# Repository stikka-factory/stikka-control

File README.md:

# Stikka-Controller

A small (42 × 23 mm, 2-layer) carrier board for an **ESP32-S3-WROOM-1** module
that turns a label printer into a network printer for the Stikka sticker
factory. The board runs the [stikka-esp32](https://github.com/stikka-factory/stikka-esp32)
firmware, which receives print jobs over MQTT from the
[stikka-mqtt](https://github.com/stikka-factory/stikka-mqtt) web app and
forwards them to the printer, normally over the printer's own USB port with
the ESP32-S3 acting as a USB host.

```
Browser (stikka-mqtt)  ──MQTT──▶  broker  ──MQTT──▶  Stikka-Controller  ──USB──▶  printer
render label, publish                                 (stikka-esp32 fw)    J7
to /<printer>/command/                                status on /<printer>/status/
```

## Repository contents

| Path | What it is |
|---|---|
| `Stikka-Controller.kicad_pro` / `.kicad_sch` / `.kicad_pcb` | KiCad project, schematic and layout |
| `bom/ibom.html` | Interactive BOM (open in a browser for assembly) |
| `production/Stikka-Controller.zip` | Gerbers + drill files for fabrication |
| `production/netlist.ipc` | IPC-D-356 netlist for fab electrical test |

## Main parts

| Ref | Part | Function |
|---|---|---|
| U1 | ESP32-S3-WROOM-1 | MCU, Wi-Fi. Use the **N16R8** variant (16 MB flash, 8 MB octal PSRAM): the firmware is built for it and needs the PSRAM. |
| U5 | RECOM R-78E5.0-1.0 footprint (schematic value says RBT10W24S05) | Switching regulator, VIN → +5 V. Feeds the printer's USB VBUS, the status LED and the LDO. |
| U2 | AP2127N-3.3 (SOT-23) | LDO, +5 V → +3.3 V for the ESP32. |
| Q1, Q2 + R1, R2 (10k) | SS8050 (SOT-23) | Classic DTR/RTS auto-program circuit, so a USB-UART adapter can reset the ESP32 and put it in download mode. |
| R3 (10k) + C1 (1µ) | | EN pull-up and power-on reset delay. |
| C11–C16 | 1µ / 4µ7 / 10µ, 0603 | Rail decoupling. |
| J7 | Grove-style 4-pin, 2.0 mm, SMD right angle | USB host port to the printer. |
| J4 | 1×5 pin header, 2.54 mm | Programming / debug UART. |
| J6 | 1×3, 2.0 mm (Samtec UMPT footprint) | External WS2812 / NeoPixel status LED. |
| J1, J2, J3 | 2-pad SMD (uses the `L_APV_ANR252010` footprint) | Reset pads, boot pads, power input. |

## Connectors and pinout

### J3: power input

| Pin | Net |
|---|---|
| 1 | VIN |
| 2 | GND |

VIN goes straight into U5. The usable input range depends on the regulator
actually fitted: an R-78E5.0-1.0 takes 7–28 V and gives up to 1 A at 5 V.
That 1 A is shared between the ESP32 and the printer's VBUS. There is no
reverse-polarity protection.

### J7: USB host to the printer

| Pin | Net | ESP32-S3 |
|---|---|---|
| 1 | GND | |
| 2 | +5V (VBUS) | |
| 3 | USB_D- | GPIO19 |
| 4 | USB_D+ | GPIO20 |
| SS1, SS2 | GND (mounting tabs) | |

This is a USB 1.1 full-speed host port on the ESP32-S3's native USB-OTG pins.
It uses a Grove housing, but it is **not I²C**, so don't plug Grove modules
into it. Wire it to a USB-A socket or straight to a USB-B plug for the
printer: GND → pin 4 (black), VBUS → pin 1 (red), D- → pin 2 (white),
D+ → pin 3 (green).

### J4: programming / debug UART

| Pin | Net | ESP32-S3 |
|---|---|---|
| 1 | TXD | GPIO43 (U0TXD), output from the board |
| 2 | RXD | GPIO44 (U0RXD), input to the board |
| 3 | DTR | Q2 emitter, Q1 base via R1 |
| 4 | RTS | Q1 emitter, Q2 base via R2 |
| 5 | GND | |

Connect a 3.3 V USB-UART adapter that exposes DTR and RTS (CP2102, CH340 and
similar): adapter RX → J4 TXD, adapter TX → J4 RXD. With DTR/RTS connected,
esptool, PlatformIO and the web flasher in stikka-mqtt reset the board into
download mode on their own. J4 has no power pin, so power the board through
J3 while flashing.

The same port carries the firmware's debug log at 115200 baud (`pio device
monitor`).

### J6: status LED

| Pin | Net | ESP32-S3 |
|---|---|---|
| 1 | +5V | |
| 2 | LED (data) | GPIO48 |
| 3 | GND | |

For a single WS2812 / NeoPixel (GRB). The LED runs from 5 V while the data
line is 3.3 V, which most WS2812Bs accept but which is below spec
(V<sub>IH</sub> = 0.7 × VDD ≈ 3.5 V). If an LED misbehaves, use a WS2812
variant that is happy with 3.3 V logic, or a level shifter.

### J1, J2: reset and boot pads

| Ref | Pin 1 | Pin 2 | Use |
|---|---|---|---|
| J1 | RST (EN) | GND | Short to reset the ESP32 |
| J2 | BOOT (GPIO0) | GND | Hold shorted while resetting to enter the ROM bootloader |

You only need these if your USB-UART adapter has no DTR/RTS.

### ESP32-S3 GPIO use

| GPIO | Net | Used for |
|---|---|---|
| EN | RST | Reset (R3/C1, Q1, J1) |
| 0 | BOOT | Strapping / download mode (Q2, J2) |
| 19 | USB_D- | USB host to printer (J7) |
| 20 | USB_D+ | USB host to printer (J7) |
| 43 | TXD | UART0 TX (J4) |
| 44 | RXD | UART0 RX (J4) |
| 48 | LED | NeoPixel data (J6) |

All other GPIOs are unconnected and not broken out.

## Firmware: stikka-esp32

Use the single `esp32-s3-devkitc-1` env from stikka-esp32's `platformio.ini`.
It targets the same N16R8 module (`qio_opi` memory type, `BOARD_HAS_PSRAM`,
16 MB partitions), so it runs on this board as is. You can flash it in
either of two ways:

- `pio run -e esp32-s3-devkitc-1 -t upload` from a stikka-esp32 checkout,
  with the USB-UART adapter on J4.
- The in-browser ESP32 flasher in the stikka-mqtt web app, over the same
  adapter.

On first boot the firmware opens a setup Wi-Fi AP, and its web wizard asks
for the printer protocol and connection method. On this board, choose:

| Method | Works on this board? | Notes |
|---|---|---|
| `usb_host` | **Yes**, the intended use | J7. The board supplies VBUS from its own 5 V rail. Covers ZPL, Brother QL and Seiko printers on USB. |
| `network` | Yes | No board hardware involved; the ESP32 talks to a ZPL printer over TCP. |
| `serial` | **No** | No UART for the printer is broken out (see below). |

### Firmware/board pin check

Checked against stikka-esp32 `3e263b6`:

| Function | Firmware | Board | Status |
|---|---|---|---|
| Status LED | NeoPixel on GPIO48, GRB (`DEFAULT_LED_*` in `platformio.ini`) | J6 pin 2 = GPIO48 | ✅ matches |
| Debug log | `Serial` = UART0, 115200 (`ARDUINO_USB_CDC_ON_BOOT=0`, `logging.cpp`) | J4 TXD/RXD = GPIO43/44 | ✅ matches |
| USB host | Native USB-OTG (`usb_host_target.cpp`) | J7 D-/D+ = GPIO19/20, VBUS = +5V | ✅ matches |
| Serial printer | UART2 on `printerUartTxPin=32` / `printerUartRxPin=33` (`config.h`) | Not broken out | ⚠️ GPIO32/33 aren't pins on the WROOM-1 module. On the N16R8 they're used internally by the flash and octal PSRAM, so this default doesn't work on this board, or on any WROOM-1 board. |

## Using it with stikka-mqtt

Once the board is on Wi-Fi and connected to the same MQTT broker as the
stikka-mqtt web app, it publishes a retained status snapshot on
`/<printerName>/status/`. The web app picks that up on its `/+/status/#`
subscription and lists the printer. Print jobs come in on
`/<printerName>/command/`, and the board's status LED shows the connection
state:

| Colour | Meaning |
|---|---|
| Green | Wi-Fi and MQTT connected |
| Yellow | Wi-Fi only |
| Red | No Wi-Fi (setup AP mode) |
| Purple / cyan flash | MQTT message received / sent |

stikka-mqtt's README documents the message format.

## Known issues / open points

- **U5 value vs footprint:** the schematic value is `RBT10W24S05`, but the
  symbol and footprint are RECOM R-78E5.0-1.0. Check which part is actually
  fitted before choosing a supply voltage.
- **J1–J3 footprint:** these use an inductor footprint (`L_APV_ANR252010`) as
  plain 2-pad SMD pads. That's fine electrically, but it's easy to miss in
  the BOM.
- **5 V budget:** with a 1 A regulator, the printer's USB port only gets what
  the ESP32 leaves over (~0.5–0.7 A while Wi-Fi is transmitting). That's
  enough for printers powered from their own supply, but not for
  bus-powered ones.
- **No serial-printer header:** if `serial` support is wanted on this board,
  a later revision would need to break out a free GPIO pair (e.g. GPIO17/18,
  the U1TXD/U1RXD defaults), and the firmware defaults would need to change
  to match.

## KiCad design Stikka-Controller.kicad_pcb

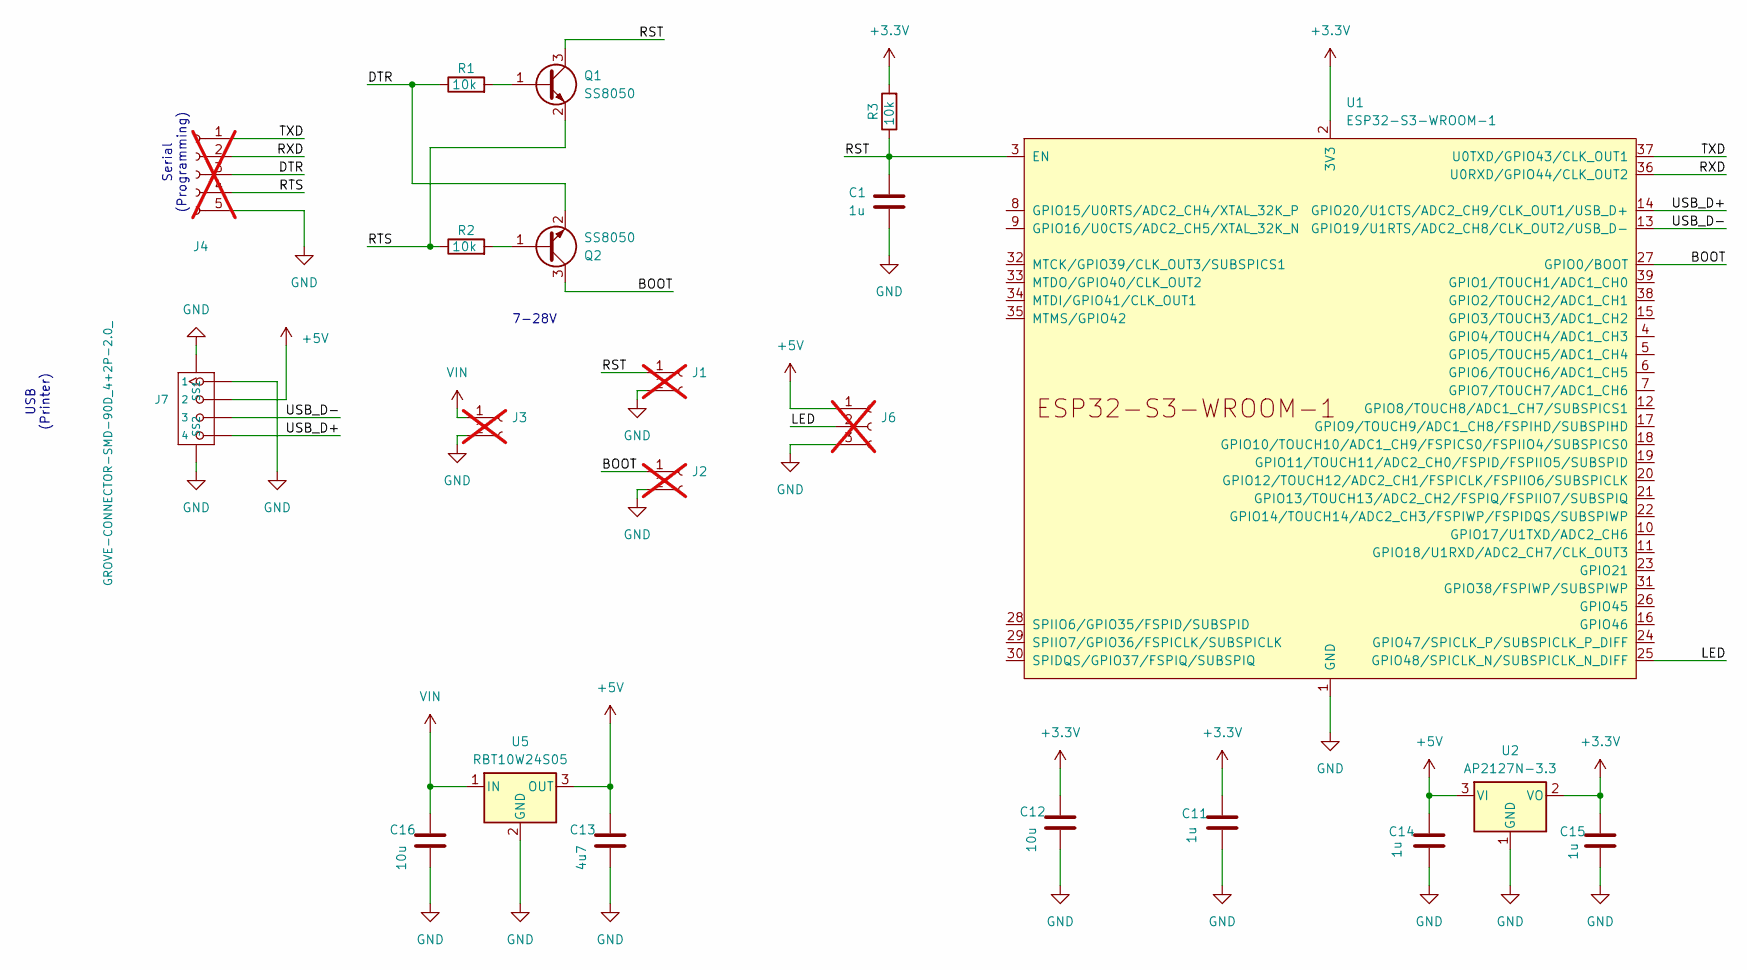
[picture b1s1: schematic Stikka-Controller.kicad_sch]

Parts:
C1, C11, C14, C15: 1u; C_0603_1608Metric_Pad1.08x0.95mm_HandSolder
C12, C16: 10u; C_0603_1608Metric_Pad1.08x0.95mm_HandSolder
C13: 4u7; C_0603_1608Metric_Pad1.08x0.95mm_HandSolder
J1, J2, J3: Conn_01x02_Socket; L_APV_ANR252010; not fitted
J4: Conn_01x05_Socket; PinHeader_1x05_P2.54mm_Vertical; not fitted
J6: Conn_01x03_Socket; Samtec_UMPT-03-XX.X-X-V-S_1x03_P2.0mm_Terminal; not fitted
J7: GROVE-CONNECTOR-SMD-90D_4+2P-2.0_; GROVE-HW4-SMD-2.0-90D
Q1, Q2: SS8050; SOT-23
R1, R2, R3: 10k; R_0603_1608Metric_Pad0.98x0.95mm_HandSolder
U1: ESP32-S3-WROOM-1
U2: AP2127N-3.3; SOT-23
U5: RBT10W24S05; Converter_DCDC_RECOM_R-78E-0.5_THT

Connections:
+3.3V: C11.1, C12.1, C15.1, R3.2, U1.2 (3V3), U2.2 (VO)
+5V: C13.1, C14.1, J6.1, J7.2, U2.3 (VI), U5.3 (OUT)
/BOOT: J2.1, Q2.3 (C), U1.27 (GPIO0/BOOT)
/DTR: J4.3, Q2.2 (E), R1.1
/LED: J6.2, U1.25 (GPIO48/SPICLK_N/SUBSPICLK_N_DIFF)
/RST: C1.1, J1.1, Q1.3 (C), R3.1, U1.3 (EN)
/RTS: J4.4, Q1.2 (E), R2.1
/RXD: J4.2, U1.36 (U0RXD/GPIO44/CLK_OUT2)
/TXD: J4.1, U1.37 (U0TXD/GPIO43/CLK_OUT1)
/USB_D+: J7.4, U1.14 (GPIO20/U1CTS/ADC2_CH9/CLK_OUT1/USB_D+)
/USB_D-: J7.3, U1.13 (GPIO19/U1RTS/ADC2_CH8/CLK_OUT2/USB_D-)
GND: C1.2, C11.2, C12.2, C13.2, C14.2, C15.2, C16.2, J1.2, J2.2, J3.2, J4.5, J6.3, J7.1, J7.5 (SS1), J7.6 (SS2), U1.1 (GND), U1.40 (GND), U1.41 (GND), U2.1 (GND), U5.2 (GND)
unnamed: Q1.1 (B), R1.2
unnamed: Q2.1 (B), R2.2
VIN: C16.1, J3.1, U5.1 (IN)

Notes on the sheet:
7-28V
Serial (Programming)
USB (Printer)

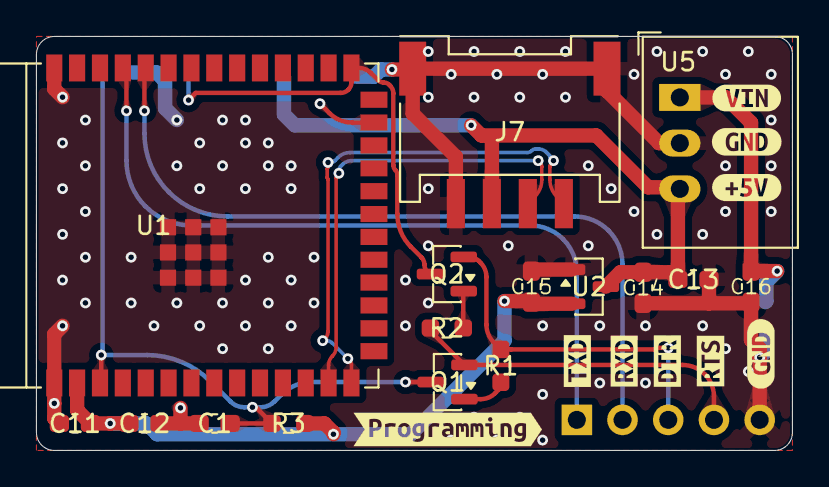
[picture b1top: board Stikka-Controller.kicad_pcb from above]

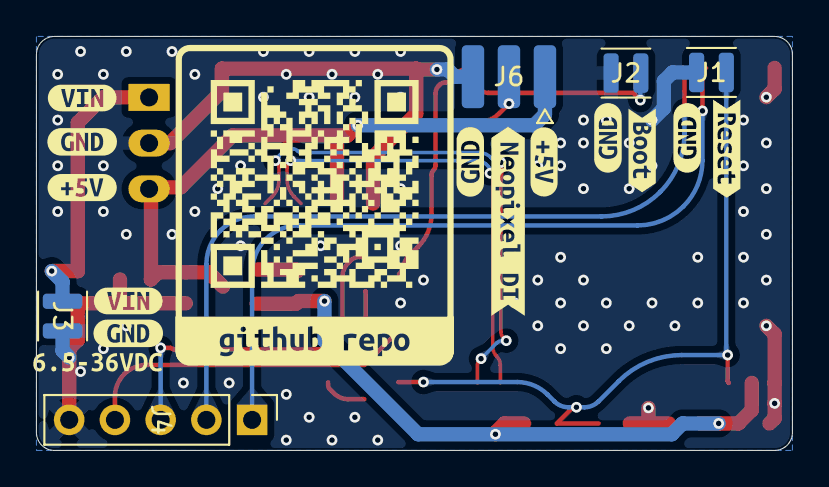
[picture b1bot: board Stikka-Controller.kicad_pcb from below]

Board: 2 copper layers, 42.0 x 23.0 mm, 44 parts (19 on the bottom side), 15 nets.

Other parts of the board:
kibuzzard-6A9B1D11: G***; kibuzzard-6A9B1D11
kibuzzard-6A99DAF3, kibuzzard-6A99DAF3#2, kibuzzard-6A99DAF3#3, kibuzzard-6A99DAF3#4, kibuzzard-6A99DAF3#5, kibuzzard-6A99DAF3#6, kibuzzard-6A99DAF3#7: G***; kibuzzard-6A99DAF3
kibuzzard-6A99DB3D, kibuzzard-6A99DB3D#2, kibuzzard-6A99DB3D#3: G***; kibuzzard-6A99DB3D
kibuzzard-6A99DB6C, kibuzzard-6A99DB6C#2, kibuzzard-6A99DB6C#3: G***; kibuzzard-6A99DB6C
kibuzzard-6A99DC93: G***; kibuzzard-6A99DC93
kibuzzard-6A99DCAC: G***; kibuzzard-6A99DCAC
kibuzzard-6A99DCB6: G***; kibuzzard-6A99DCB6
kibuzzard-6A99DCCC: G***; kibuzzard-6A99DCCC
kibuzzard-6A99DCF5: G***; kibuzzard-6A99DCF5
kibuzzard-6A99DDB5: G***; kibuzzard-6A99DDB5
kibuzzard-6A99DDFF: G***; kibuzzard-6A99DDFF
kibuzzard-6A99E40F: G***; kibuzzard-6A99E40F
kobee-studio-6A9B380E: Kobee Studio; kobee-studio-6A9B380E
